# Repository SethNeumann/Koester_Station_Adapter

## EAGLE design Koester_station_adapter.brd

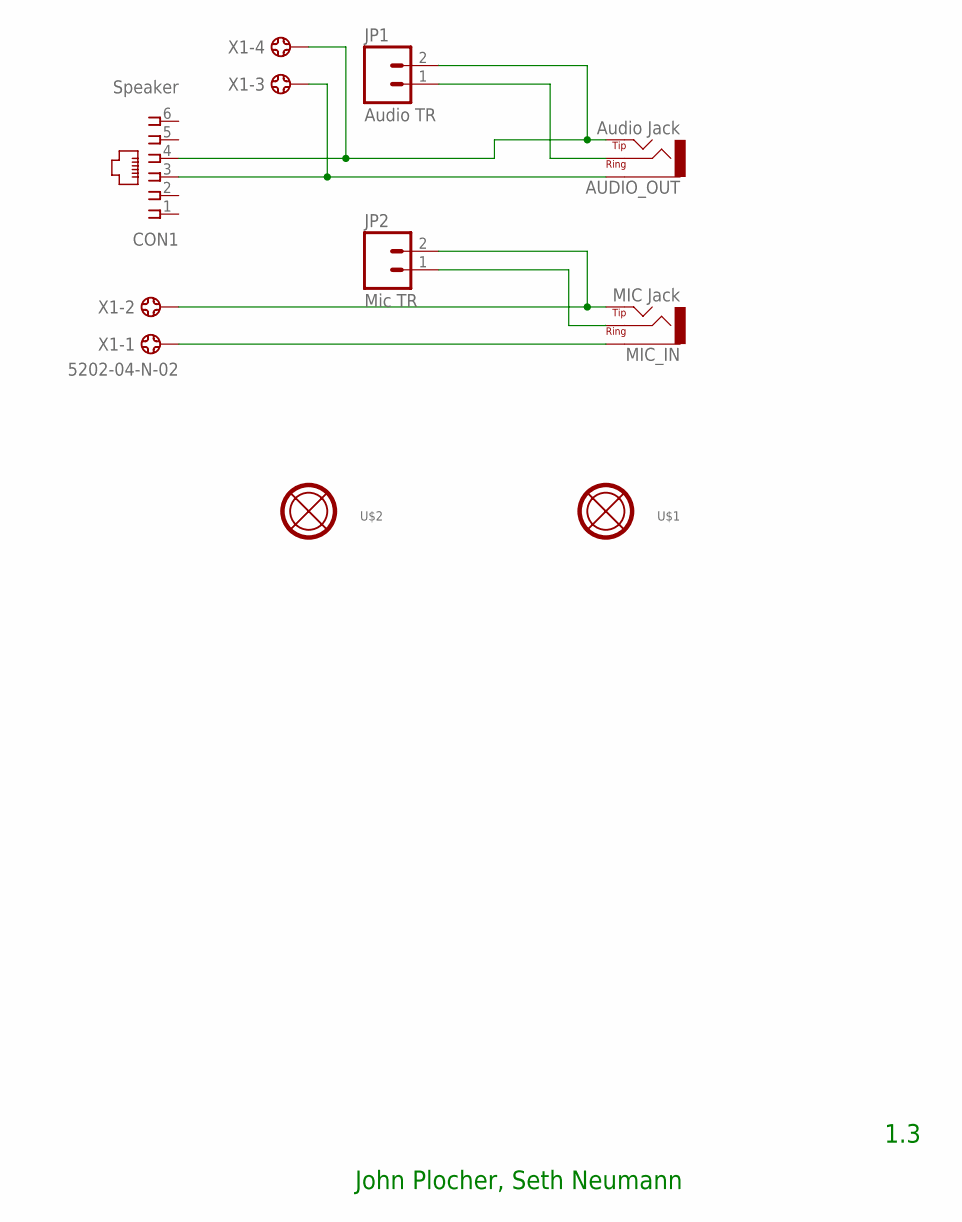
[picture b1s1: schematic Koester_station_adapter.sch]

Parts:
AUDIO_OUT: Audio Jack; AUDIO-JACK-3.5MM_STEREO
CON1: Speaker; RJ25-INVERTED
JP1: Audio TR; MOLEX-1X2_LOCK
JP2: Mic TR; MOLEX-1X2_LOCK
MIC_IN: MIC Jack; AUDIO-JACK-3.5MM_STEREO
U$1, U$2: MOUNTINGHOLE
X1: 5202-04-N-02

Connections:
MIC_SLEEVE: MIC_IN.GND (SLEEVE), X1.1
MIC_TIP: JP2.2 (B), MIC_IN.TIP, X1.2
unnamed: AUDIO_OUT.RING, JP1.1 (A)
unnamed: JP2.1 (A), MIC_IN.RING
OUT_SLEEVE: AUDIO_OUT.GND (SLEEVE), CON1.3, X1.3
OUT_TIP: AUDIO_OUT.TIP, CON1.4, JP1.2 (B), X1.4

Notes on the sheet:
John Plocher, Seth Neumann
1.3

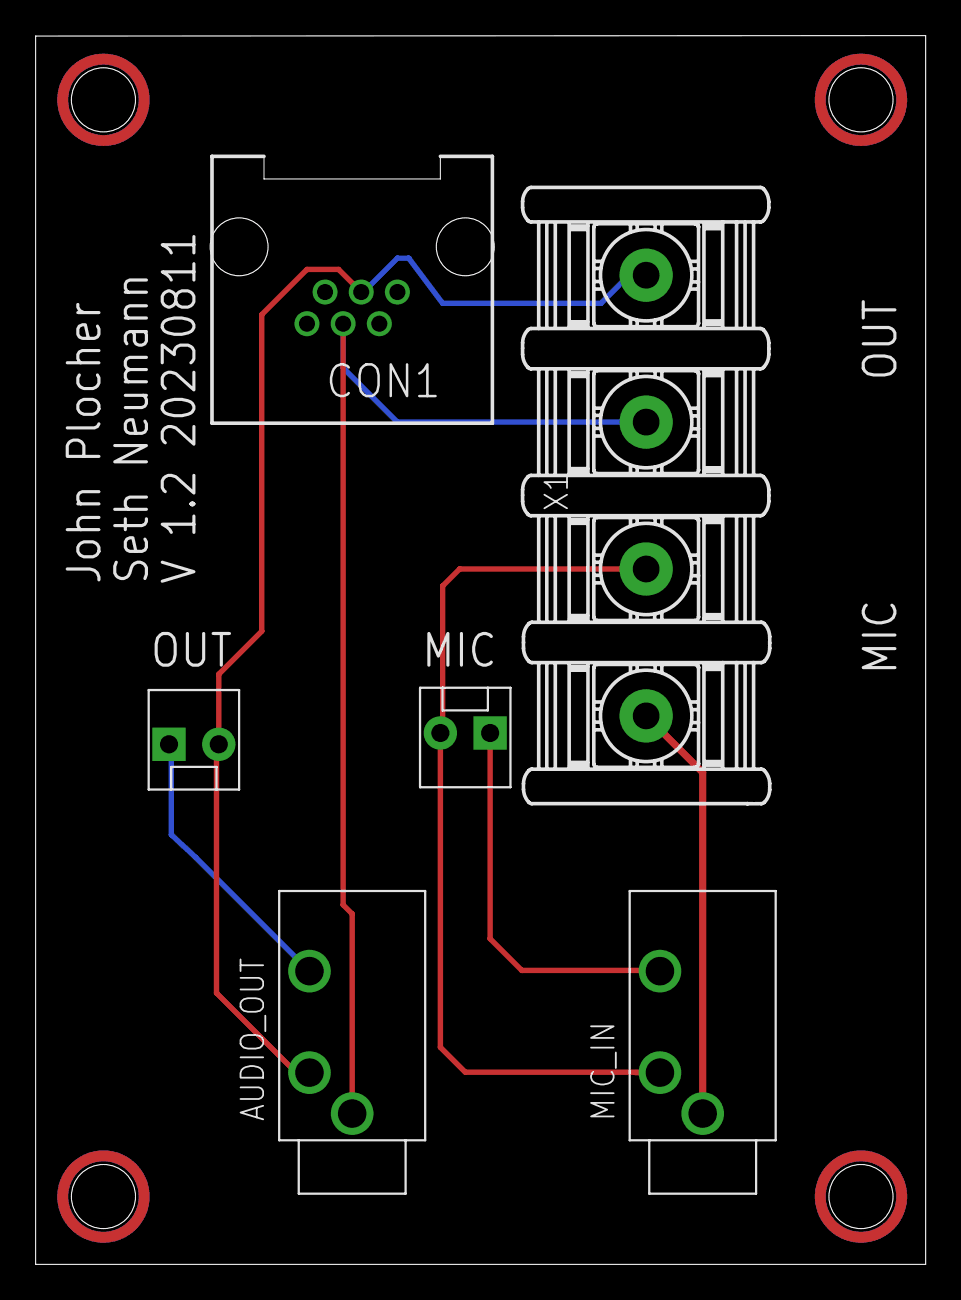
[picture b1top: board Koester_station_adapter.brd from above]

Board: 2 copper layers, 50.0 x 69.0 mm, 13 parts (0 on the bottom side), 6 nets.

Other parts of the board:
U$3, U$4: MOUNTINGHOLE
U$5: MRCSLOGOTOP
U$6: MRCSLOGOBTM
U$7: CA-PROP65WARNING

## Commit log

2019-11-26 the board in the DIN rail not the phone
2023-09-14 Version 1.2
    Replaced brass screws on board with 6mm terminal strip
